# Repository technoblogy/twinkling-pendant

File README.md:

# Twinkling Pendant
A star-shaped pendant with six coloured LEDs that twinkle in a random pattern.

See <http://www.technoblogy.com/show?3RMX>.

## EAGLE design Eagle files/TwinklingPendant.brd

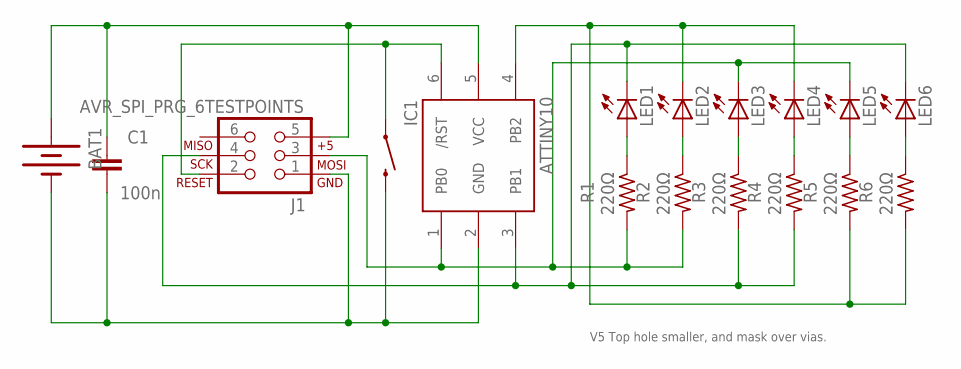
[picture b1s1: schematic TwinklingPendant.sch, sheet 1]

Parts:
BAT1: BATTERY12MM; BATTCON_12MM
C1: 100n; 0603-CAP
IC1: ATTINY10; SOT23-6
J1: AVR_SPI_PRG_6TESTPOINTS; 2X3_TEST_POINTS
LED1, LED2, LED3, LED4, LED5, LED6: LEDCHIPLED_0805; CHIPLED_0805
R1, R2, R3, R4, R5, R6: 220Ω; R0805
S2: SWITCH-MOMENTARY-2SMD; TACTILE-SWITCH-SMD

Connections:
unnamed: BAT1.PWR@1 (+), C1.1, IC1.5 (VCC), J1.5
unnamed: IC1.6 (/RST), J1.2, S2.1
unnamed: LED2.A, R2.1
unnamed: LED1.A, R1.1
unnamed: LED3.A, R3.1
unnamed: IC1.1 (PB0), J1.3, LED3.C, LED5.C, R1.2, R2.2
unnamed: BAT1.GND (-), C1.2, IC1.2 (GND), J1.1, S2.3 (2)
unnamed: IC1.4 (PB2), LED2.C, LED4.C, R5.2, R6.2
unnamed: LED4.A, R4.1
unnamed: LED5.A, R5.1
unnamed: LED6.A, R6.1
unnamed: IC1.3 (PB1), J1.4, LED1.C, LED6.C, R3.2, R4.2

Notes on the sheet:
V5 Top hole smaller, and mask over vias.

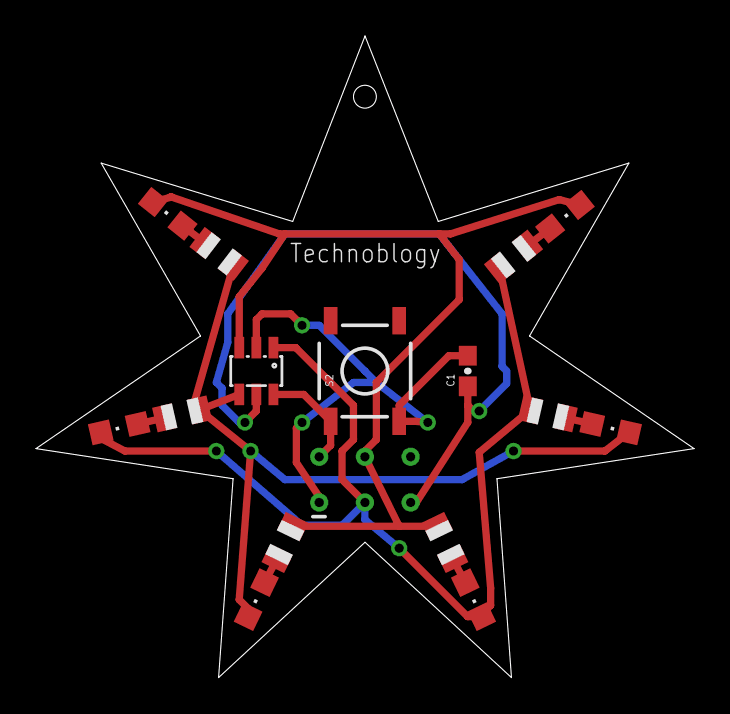
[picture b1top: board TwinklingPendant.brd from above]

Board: 2 copper layers, 36.6 x 35.6 mm, 17 parts (1 on the bottom side), 12 nets.

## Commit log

2022-02-23 Version 1 - 23rd February 2022

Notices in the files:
parts and their libraries:
SparkFun-Capacitors: Licensing: CC v3.0 Share-Alike You are welcome to use this library for commercial purposes.
SparkFun-Electromechanical: Licensing: Creative Commons ShareAlike 4.0 International - https://creativecommons.org/licenses/by-sa/4.0
